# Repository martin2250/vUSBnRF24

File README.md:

# vUSBnRF24
a USB adapter for the popular (and cheap!) NRF24L01+ module

please note that with the current software, only clients with AA enabled or RX_PW set to DYNPD can receive transmissions from the dongle

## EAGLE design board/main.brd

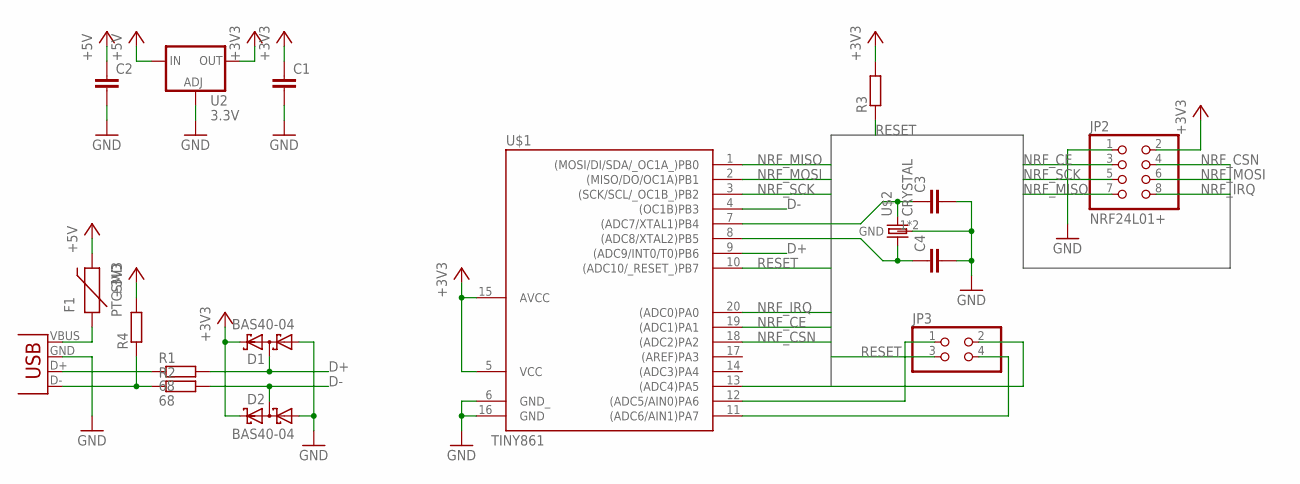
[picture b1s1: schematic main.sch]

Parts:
C1, C2: C-EUC1206; C1206
C3, C4: C-EUC0805; C0805
D1, D2: BAS40-04; SOT23
F1: PTCSMD; PTC-1206
JP1: USB-A-H
JP2: NRF24L01+; 2X04
JP3: PINHD-2X2; 2X02
R1, R2: 68; R1206
R3, R4: R-EU_R1206; R1206
U2: 3.3V; SOT223
U$1: TINY861; SO20L$
U$2: CRYSTAL; 5X7

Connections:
+3V3: C1.1, D1.2 (C2), D2.2 (C2), JP2.2, R3.2, R4.2, U2.2 (OUT), U$1.5 (VCC), U$1.15 (AVCC)
+5V: C2.1, F1.2, U2.3 (IN)
D+: D1.3 (C1A2), R1.2, U$1.9 ((ADC9/INT0/T0)PB6)
D-: D2.3 (C1A2), R2.2, U$1.4 ((OC1B)PB3)
GND: C1.2, C2.2, C3.2, C4.2, D1.1 (A1), D2.1 (A1), JP1.GND (VBUS), JP2.1, U2.1 (ADJ), U$1.6 (GND_), U$1.16 (GND), U$2.1 (GND), U$2.3 (GND)
unnamed: F1.1, JP1.VBUS (GND)
unnamed: C3.1, U$1.7 ((ADC7/XTAL1)PB4), U$2.4 (2)
unnamed: JP1.D+ (D-), R1.1
unnamed: JP1.D- (D+), R2.1, R4.1
unnamed: C4.1, U$1.8 ((ADC8/XTAL2)PB5), U$2.2 (1)
unnamed: JP3.4, U$1.11 ((ADC6/AIN1)PA7)
unnamed: JP3.1, U$1.12 ((ADC5/AIN0)PA6)
unnamed: JP3.2, U$1.13 ((ADC4)PA5)
NRF_CE: JP2.3, U$1.19 ((ADC1)PA1)
NRF_CSN: JP2.4, U$1.18 ((ADC2)PA2)
NRF_IRQ: JP2.8, U$1.20 ((ADC0)PA0)
NRF_MISO: JP2.7, U$1.1 ((MOSI/DI/SDA/_OC1A_)PB0)
NRF_MOSI: JP2.6, U$1.2 ((MISO/DO/OC1A)PB1)
NRF_SCK: JP2.5, U$1.3 ((SCK/SCL/_OC1B_)PB2)
RESET: JP3.3, R3.1, U$1.10 ((ADC10/_RESET_)PB7)

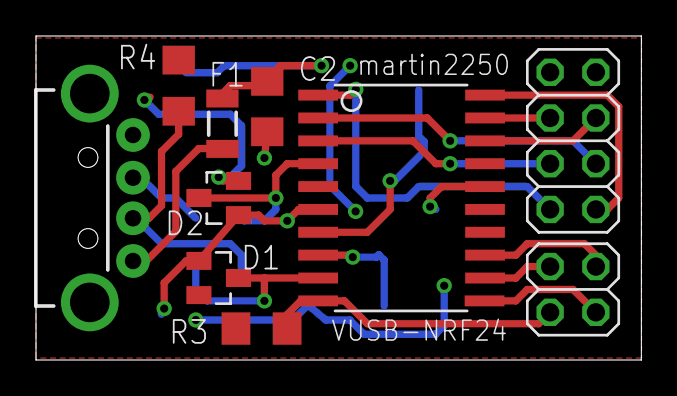
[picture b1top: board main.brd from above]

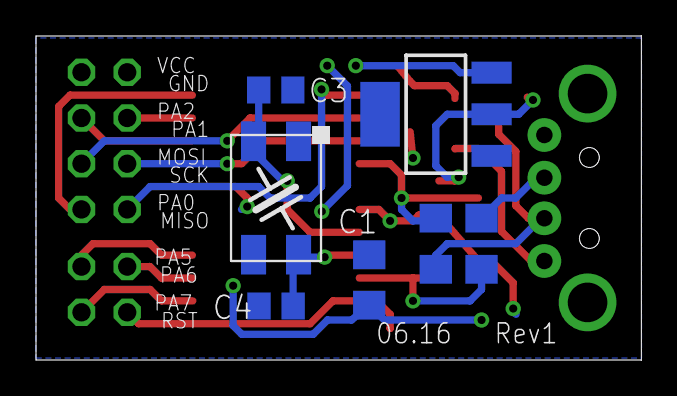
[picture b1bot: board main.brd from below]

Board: 2 copper layers, 33.6 x 18.0 mm, 17 parts (7 on the bottom side), 20 nets.

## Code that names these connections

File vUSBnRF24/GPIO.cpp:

#include <avr/io.h>

#include "GPIO.h"

#define SS_REG PORTA
#define SS_PIN PA2

#define CE_REG PORTA
#define CE_PIN PA1

#define IRQ_REG PINA
#define IRQ_PIN PA0

void GPIO::SS::high()
{
	SS_REG |= _BV(SS_PIN);
}

void GPIO::SS::low()
{
	SS_REG &= ~_BV(SS_PIN);
}

bool GPIO::SS::get()
{
	return (SS_REG >> SS_PIN) & 0x01;
}

void GPIO::CE::high()
{
	CE_REG |= _BV(CE_PIN);
}

void GPIO::CE::low()
{
	CE_REG &= ~_BV(CE_PIN);
}

bool GPIO::CE::get()
{
	return (CE_REG >> CE_PIN) & 0x01;
}

bool GPIO::IRQ::get()
{
	return (IRQ_REG >> IRQ_PIN) & 0x01;
}

void GPIO::init()
{
	PORTA = 0;
	PORTB = 0;

	DDRA = _BV(PA1) | _BV(PA2);
	DDRB = _BV(PB1) | _BV(PB2);

	PORTA = _BV(PA0) | _BV(PA2);	//IRQ pullup, SS

	USICR = _BV(USIWM0);
}

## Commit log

2016-08-05 :lollipop: Added .gitattributes & .gitignore files
2016-08-05 added board
2016-08-05 added acknowledge to status
2016-08-06 fixed TX
    -removed acks
    -multiple packets for the same recipient in buffer at a time
    -added flushTX after MAX_RT (only packets for this recipient are lost)
    -fixed error in config
2016-08-06 added check for RX_PW
2016-08-06 flushRX clears rxdataavailable
2016-08-06 added 'rx buffer available' flag in RXPacket
2016-08-06 corrected protocol
2016-08-07 fixed config for 250kbps mode

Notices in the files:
parts and their libraries:
SparkFun-PowerIC: Licensing: Creative Commons ShareAlike 4.0 International - https://creativecommons.org/licenses/by-sa/4.0
